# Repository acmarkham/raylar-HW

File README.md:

# raylar-HW
## Caracal Raylar Hardware Repo

This is the main repository for the bioacoustic platform Caracal Raylar. This is an updated version of the CARACAL EVO (2021) design, which itself is an evolution of SHUMBA (2019). The main features are:

- Six onboard microphones, low frequency rolloff 7Hz
- microSD card for storage
- Onboard GPS for precision timestamping and location
- Onboard dual band wireless (sub-GHz plus 2.4GHz) for mesh networking
- STM32U5 core, supports up to 3.5MB RAM depending on variant
- Multi-source power tree including
  - USB
  - Solar
  - Rechargeable single cell lipo
  - External battery 6V-12V
- Onboard accelerometer and magnetometer/compass for tilt and direction
- Extension connectors: 
  - QWIIC x 2 (easy to plug in peripherals like a OLED display) 
  - Mikrobus MBUS (supports a huge ecosystem of sensors)
  - EXT
  - DEBUG
- Beeper/LEDs for user feedback (errors, status etc)

## PCB

## Schematic

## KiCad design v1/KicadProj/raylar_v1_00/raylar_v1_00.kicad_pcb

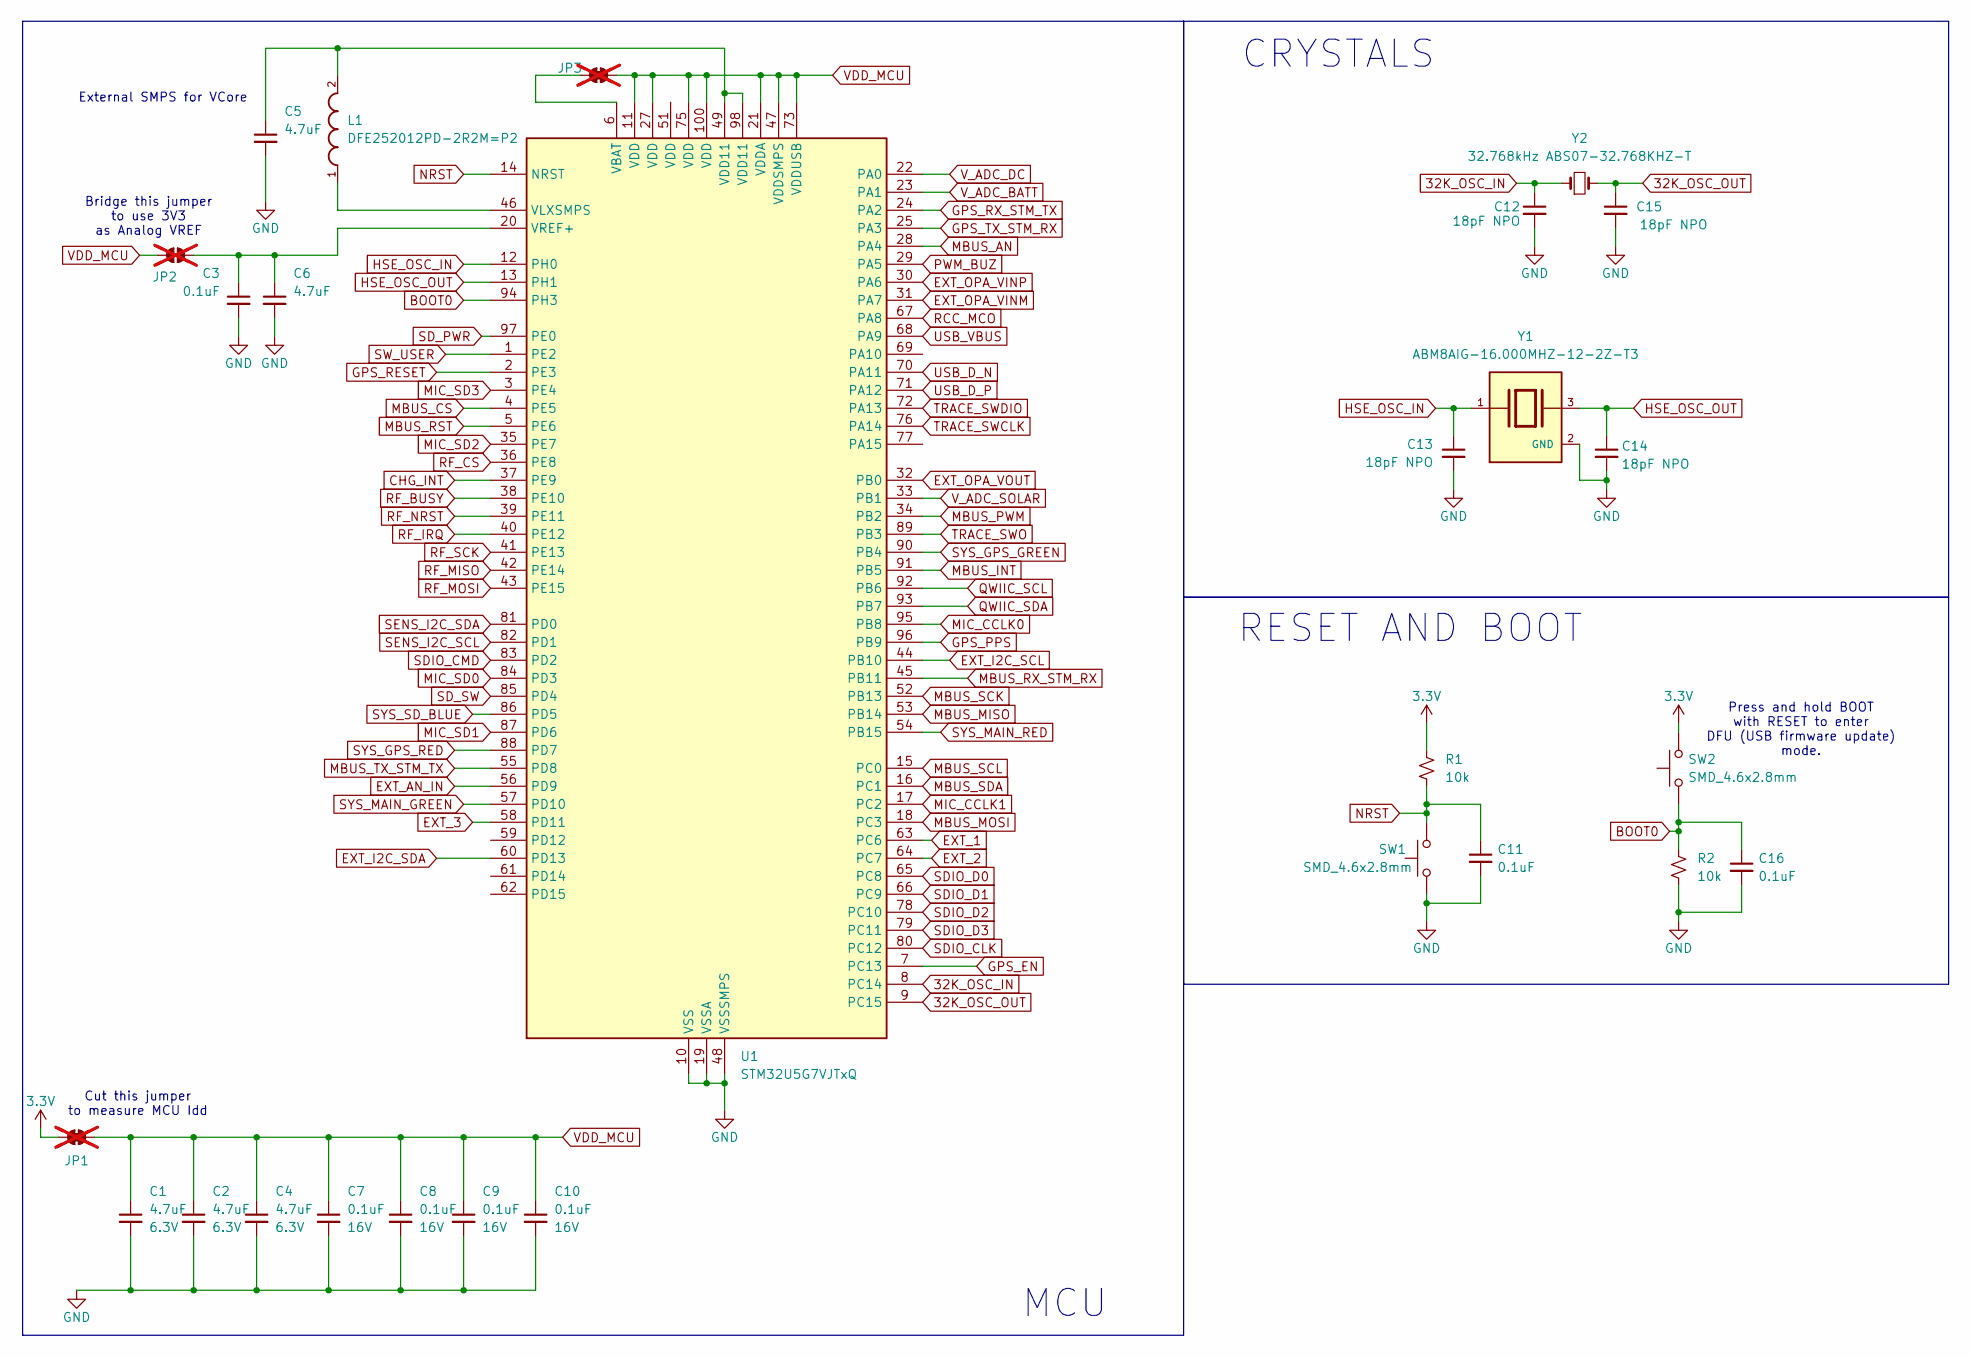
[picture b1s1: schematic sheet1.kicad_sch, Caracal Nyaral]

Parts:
C1, C2, C4, C5, C6: 4.7uF; C_0402_1005Metric; Voltage 6.3V; Tolerance 20%; LCSC C23733
C3, C7, C8, C9, C10, C11, C16: 0.1uF; C_0402_1005Metric; Voltage 16V; Tolerance 10%; LCSC C77020
C12, C13, C14, C15: 18pF NPO; C_0402_1005Metric; Voltage 50V; Tolerance 5%; LCSC C106202
JP1, JP3: Jumper_2_NC_Trace; not fitted
JP2: Jumper_2_NO; not fitted
L1: DFE252012PD-2R2M=P2; INDC2520X120N; Digikey 490-DFE252012PD-2R2M=P2DKR-ND
R1, R2: 10k; R_0402_1005Metric; LCSC C60489
SW1, SW2: SMD_4.6x2.8mm; Push_SMD_4.6x2.8mm_h1.9mm; Mfg Part# KMR231NGLFS; LCSC C221676
U1: STM32U5G7VJTxQ; LQFP-100_14x14mm_P0.5mm; LCSC C24591629
Y1: ABM8AIG-16.000MHZ-12-2Z-T3; XTAL_ABM8AIG-16.000MHZ-12-2Z-T3; PARTREV 43629; LCSC C596903
Y2: 32.768kHz ABS07-32.768KHZ-T; Crystal_SMD_3.2x1.5mm; LCSC C130253

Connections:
3.3V: JP1.1 (A), R1.2, SW2.2; also elsewhere on the board
32K_OSC_IN: C12.1, U1.8 (PC14), Y2.1
32K_OSC_OUT: C15.1, U1.9 (PC15), Y2.2
BOOT0: C16.1, R2.2, SW2.1, U1.94 (PH3)
CHG_INT: U1.37 (PE9); also elsewhere on the board
EXT_1: U1.63 (PC6); also elsewhere on the board
EXT_2: U1.64 (PC7); also elsewhere on the board
EXT_3: U1.58 (PD11); also elsewhere on the board
EXT_AN_IN: U1.56 (PD9); also elsewhere on the board
EXT_I2C_SCL: U1.44 (PB10); also elsewhere on the board
EXT_I2C_SDA: U1.60 (PD13); also elsewhere on the board
EXT_OPA_VINM: U1.31 (PA7); also elsewhere on the board
EXT_OPA_VINP: U1.30 (PA6); also elsewhere on the board
EXT_OPA_VOUT: U1.32 (PB0); also elsewhere on the board
GND: C1.2, C2.2, C3.2, C4.2, C5.2, C6.2, C7.2, C8.2, C9.2, C10.2, C11.2, C12.2, C13.2, C14.2, C15.2, C16.2, R2.1, SW1.1, U1.10 (VSS), U1.19 (VSSA), U1.26 (VSS), U1.48 (VSSSMPS), U1.50 (VSS), U1.74 (VSS), U1.99 (VSS), Y1.2 (GND), Y1.4 (GND); also elsewhere on the board
GPS_EN: U1.7 (PC13); also elsewhere on the board
GPS_PPS: U1.96 (PB9); also elsewhere on the board
GPS_RESET: U1.2 (PE3); also elsewhere on the board
GPS_RX_STM_TX: U1.24 (PA2); also elsewhere on the board
GPS_TX_STM_RX: U1.25 (PA3); also elsewhere on the board
HSE_OSC_IN: C13.1, U1.12 (PH0), Y1.1
HSE_OSC_OUT: C14.1, U1.13 (PH1), Y1.3
MBUS_AN: U1.28 (PA4); also elsewhere on the board
MBUS_CS: U1.4 (PE5); also elsewhere on the board
MBUS_INT: U1.91 (PB5); also elsewhere on the board
MBUS_MISO: U1.53 (PB14); also elsewhere on the board
MBUS_MOSI: U1.18 (PC3); also elsewhere on the board
MBUS_PWM: U1.34 (PB2); also elsewhere on the board
MBUS_RST: U1.5 (PE6); also elsewhere on the board
MBUS_RX_STM_RX: U1.45 (PB11); also elsewhere on the board
MBUS_SCK: U1.52 (PB13); also elsewhere on the board
MBUS_SCL: U1.15 (PC0); also elsewhere on the board
MBUS_SDA: U1.16 (PC1); also elsewhere on the board
MBUS_TX_STM_TX: U1.55 (PD8); also elsewhere on the board
MIC_CCLK0: U1.95 (PB8); also elsewhere on the board
MIC_CCLK1: U1.17 (PC2); also elsewhere on the board
MIC_SD0: U1.84 (PD3); also elsewhere on the board
MIC_SD1: U1.87 (PD6); also elsewhere on the board
MIC_SD2: U1.35 (PE7); also elsewhere on the board
MIC_SD3: U1.3 (PE4); also elsewhere on the board
NRST: C11.1, R1.1, SW1.2, U1.14 (NRST); also elsewhere on the board
unnamed: C5.1, L1.2, U1.49 (VDD11), U1.98 (VDD11)
unnamed: C3.1, C6.1, JP2.2 (B), U1.20 (VREF+)
unnamed: JP3.1 (A), U1.6 (VBAT)
unnamed: L1.1, U1.46 (VLXSMPS)
PWM_BUZ: U1.29 (PA5); also elsewhere on the board
QWIIC_SCL: U1.92 (PB6); also elsewhere on the board
QWIIC_SDA: U1.93 (PB7); also elsewhere on the board
RCC_MCO: U1.67 (PA8); also elsewhere on the board
RF_BUSY: U1.38 (PE10); also elsewhere on the board
RF_CS: U1.36 (PE8); also elsewhere on the board
RF_IRQ: U1.40 (PE12); also elsewhere on the board
RF_MISO: U1.42 (PE14); also elsewhere on the board
RF_MOSI: U1.43 (PE15); also elsewhere on the board
RF_NRST: U1.39 (PE11); also elsewhere on the board
RF_SCK: U1.41 (PE13); also elsewhere on the board
SDIO_CLK: U1.80 (PC12); also elsewhere on the board
SDIO_CMD: U1.83 (PD2); also elsewhere on the board
SDIO_D0: U1.65 (PC8); also elsewhere on the board
SDIO_D1: U1.66 (PC9); also elsewhere on the board
SDIO_D2: U1.78 (PC10); also elsewhere on the board
SDIO_D3: U1.79 (PC11); also elsewhere on the board
SD_PWR: U1.97 (PE0); also elsewhere on the board
SD_SW: U1.85 (PD4); also elsewhere on the board
SENS_I2C_SCL: U1.82 (PD1); also elsewhere on the board
SENS_I2C_SDA: U1.81 (PD0); also elsewhere on the board
SW_USER: U1.1 (PE2); also elsewhere on the board
SYS_GPS_GREEN: U1.90 (PB4); also elsewhere on the board
SYS_GPS_RED: U1.88 (PD7); also elsewhere on the board
SYS_MAIN_GREEN: U1.57 (PD10); also elsewhere on the board
SYS_MAIN_RED: U1.54 (PB15); also elsewhere on the board
SYS_SD_BLUE: U1.86 (PD5); also elsewhere on the board
TRACE_SWCLK: U1.76 (PA14); also elsewhere on the board
TRACE_SWDIO: U1.72 (PA13); also elsewhere on the board
TRACE_SWO: U1.89 (PB3); also elsewhere on the board
USB_D_N: U1.70 (PA11); also elsewhere on the board
USB_D_P: U1.71 (PA12); also elsewhere on the board
USB_VBUS: U1.68 (PA9); also elsewhere on the board
VDD_MCU: C1.1, C2.1, C4.1, C7.1, C8.1, C9.1, C10.1, JP1.2 (B), JP2.1 (A), JP3.2 (B), U1.11 (VDD), U1.21 (VDDA), U1.27 (VDD), U1.47 (VDDSMPS), U1.73 (VDDUSB), U1.75 (VDD), U1.100 (VDD)
V_ADC_BATT: U1.23 (PA1); also elsewhere on the board
V_ADC_DC: U1.22 (PA0); also elsewhere on the board
V_ADC_SOLAR: U1.33 (PB1); also elsewhere on the board

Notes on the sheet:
Press and hold BOOT with RESET to enter DFU (USB firmware update) mode.
CRYSTALS
MCU
Bridge this jumper to use 3V3 as Analog VREF
Cut this jumper to measure MCU Idd
RESET AND BOOT
External SMPS for VCore

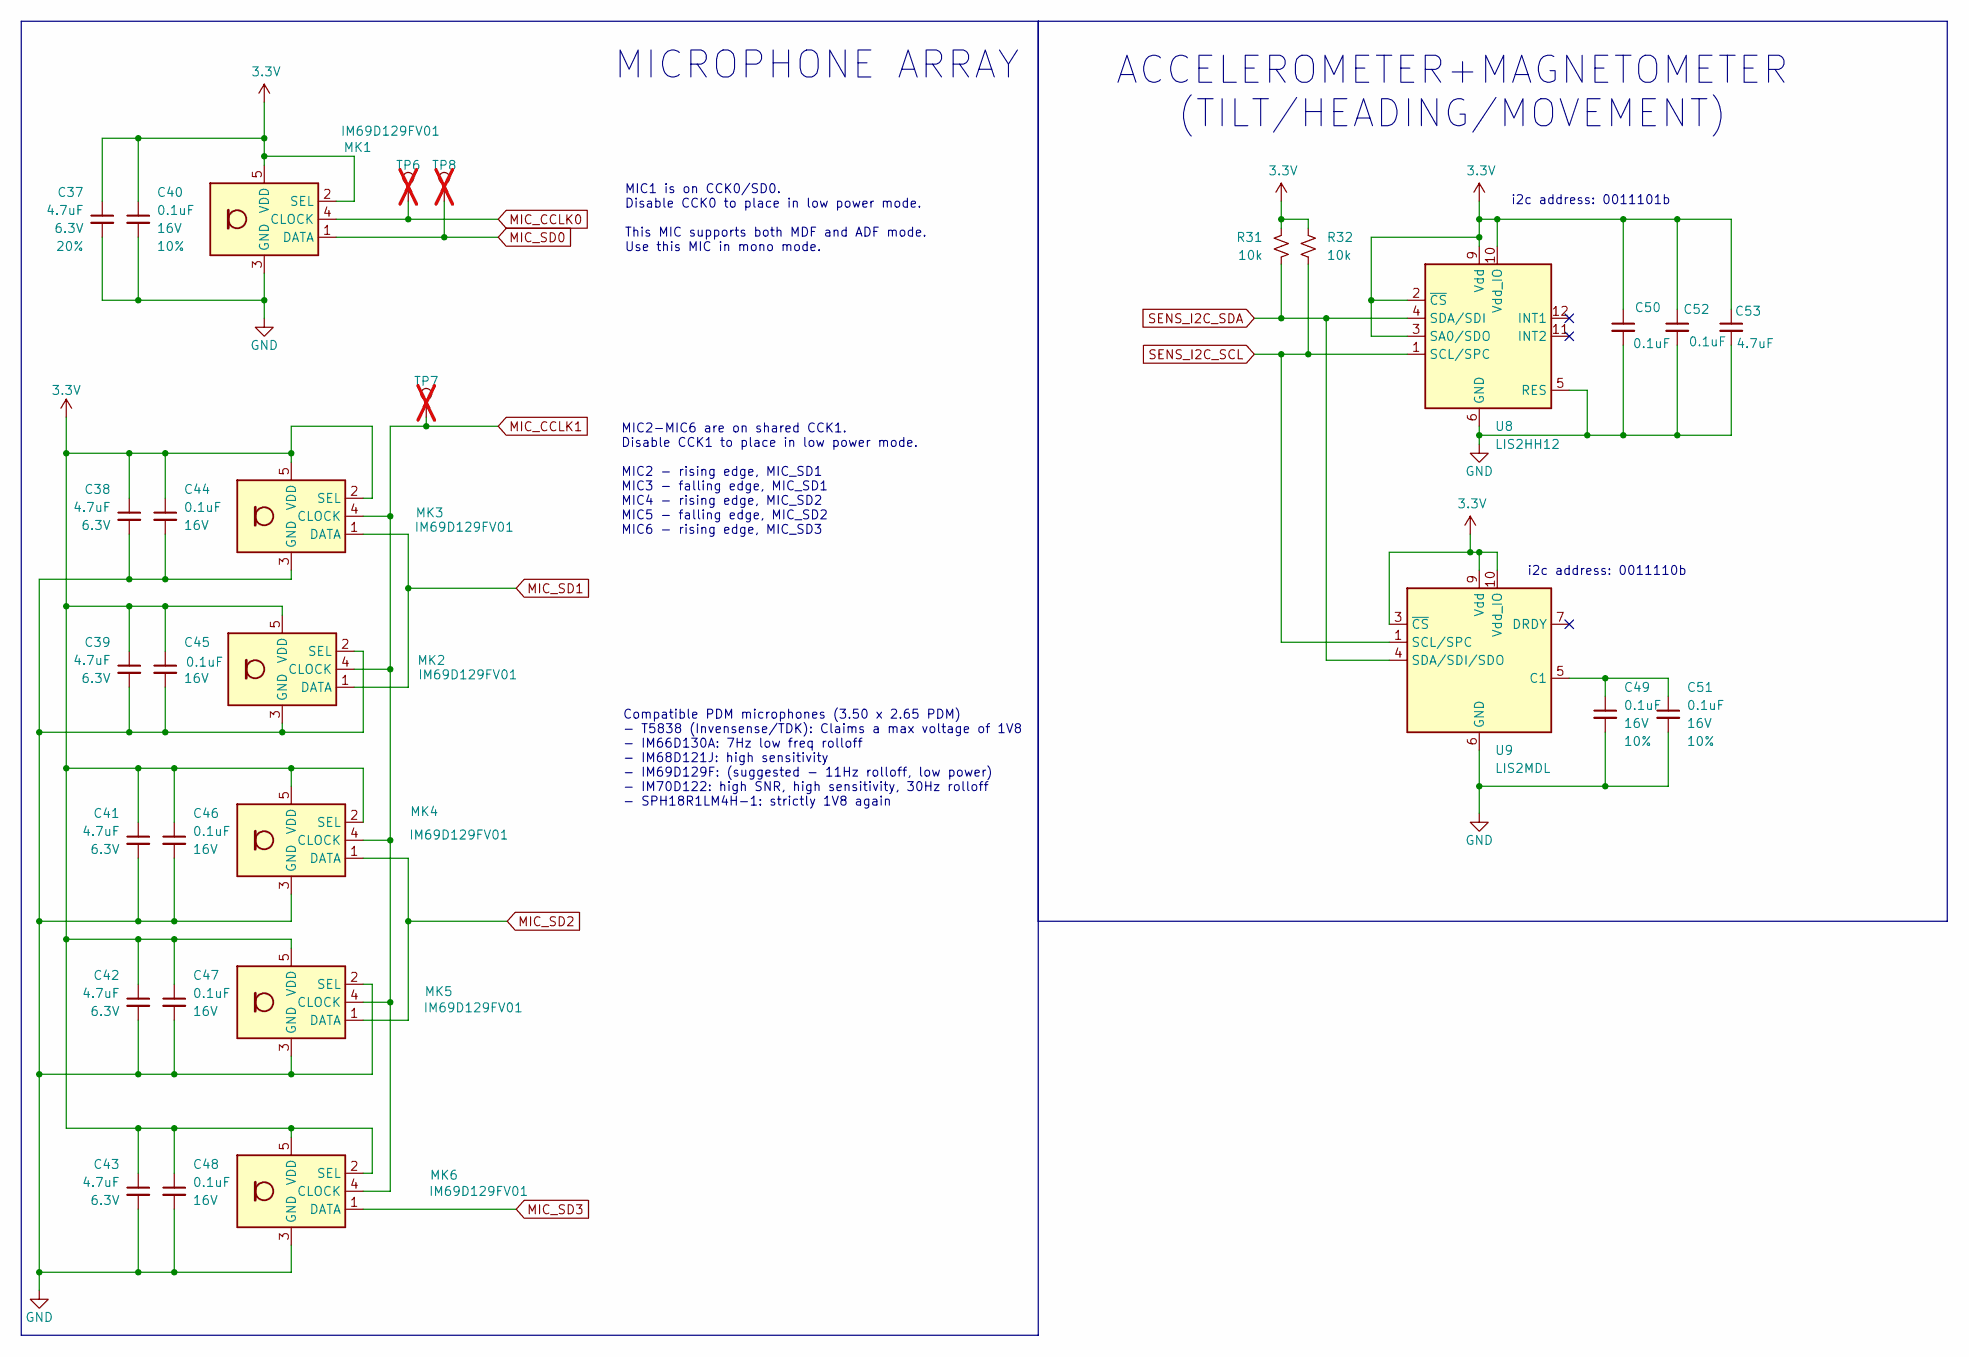
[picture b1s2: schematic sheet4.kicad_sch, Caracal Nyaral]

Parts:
C37, C38, C39, C41, C42, C43, C53: 4.7uF; C_0402_1005Metric; Voltage 6.3V; Tolerance 20%; LCSC C23733
C40, C44, C45, C46, C47, C48, C49, C50, C51, C52: 0.1uF; C_0402_1005Metric; Voltage 16V; Tolerance 10%; LCSC C77020
MK1, MK2, MK3, MK4, MK5, MK6: IM69D129FV01; Knowles_LGA-5_3.5x2.65mm; Digikey 448-IM69D129FV01XTMA1DKR-ND
R31, R32: 10k; R_0402_1005Metric; LCSC C60489
TP6, TP7, TP8: 0.5mm; TestPoint-0.5mm; not fitted
U8: LIS2HH12; LGA-12_2x2mm_P0.5mm; LCSC C221446
U9: LIS2MDL; LGA-12_2x2mm_P0.5mm; LCSC C919695

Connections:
3.3V: C37.1, C38.1, C39.1, C40.1, C41.1, C42.1, C43.1, C44.1, C45.1, C46.1, C47.1, C48.1, C50.1, C52.1, C53.1, MK1.2 (SEL), MK1.5 (VDD), MK2.5 (VDD), MK3.2 (SEL), MK3.5 (VDD), MK4.2 (SEL), MK4.5 (VDD), MK5.5 (VDD), MK6.2 (SEL), MK6.5 (VDD), R31.2, R32.2, U8.2 (~CS), U8.3 (SA0/SDO), U8.9 (Vdd), U8.10 (Vdd_IO), U9.3 (~CS), U9.9 (Vdd), U9.10 (Vdd_IO); also elsewhere on the board
GND: C37.2, C38.2, C39.2, C40.2, C41.2, C42.2, C43.2, C44.2, C45.2, C46.2, C47.2, C48.2, C49.2, C50.2, C51.2, C52.2, C53.2, MK1.3 (GND), MK2.2 (SEL), MK2.3 (GND), MK3.3 (GND), MK4.3 (GND), MK5.2 (SEL), MK5.3 (GND), MK6.3 (GND), U8.5 (RES), U8.6 (GND), U8.7 (GND), U8.8 (GND), U9.6 (GND), U9.8 (GND); also elsewhere on the board
MIC_CCLK0: MK1.4 (CLOCK), TP6.1; also elsewhere on the board
MIC_CCLK1: MK2.4 (CLOCK), MK3.4 (CLOCK), MK4.4 (CLOCK), MK5.4 (CLOCK), MK6.4 (CLOCK), TP7.1; also elsewhere on the board
MIC_SD0: MK1.1 (DATA), TP8.1; also elsewhere on the board
MIC_SD1: MK2.1 (DATA), MK3.1 (DATA); also elsewhere on the board
MIC_SD2: MK4.1 (DATA), MK5.1 (DATA); also elsewhere on the board
MIC_SD3: MK6.1 (DATA); also elsewhere on the board
unnamed: C49.1, C51.1, U9.5 (C1)
SENS_I2C_SCL: R32.1, U8.1 (SCL/SPC), U9.1 (SCL/SPC); also elsewhere on the board
SENS_I2C_SDA: R31.1, U8.4 (SDA/SDI), U9.4 (SDA/SDI/SDO); also elsewhere on the board

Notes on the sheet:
MICROPHONE ARRAY
Compatible PDM microphones (3.50 x 2.65 PDM) - T5838 (Invensense/TDK): Claims a max voltage of 1V8 - IM66D130A: 7Hz low freq rolloff - IM68D121J: high sensitivity - IM69D129F: (suggested - 11Hz rolloff, low power) - IM70D122: high SNR, high sensitivity, 30Hz rolloff - SPH18R1LM4H-1: strictly 1V8 ag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
i2c address: 0011101b
MIC2-MIC6 are on shared CCK1. Disable CCK1 to place in low power mode. MIC2 - rising edge, MIC_SD1 MIC3 - falling edge, MIC_SD1 MIC4 - rising edge, MIC_SD2 MIC5 - falling edge, MIC_SD2 MIC6 - rising edge, MIC_SD3
i2c address: 0011110b
MIC1 is on CCK0/SD0. Disable CCK0 to place in low power mode. This MIC supports both MDF and ADF mode. Use this MIC in mono mode.
ACCELEROMETER+MAGNETOMETER (TILT/HEADING/MOVEMENT)

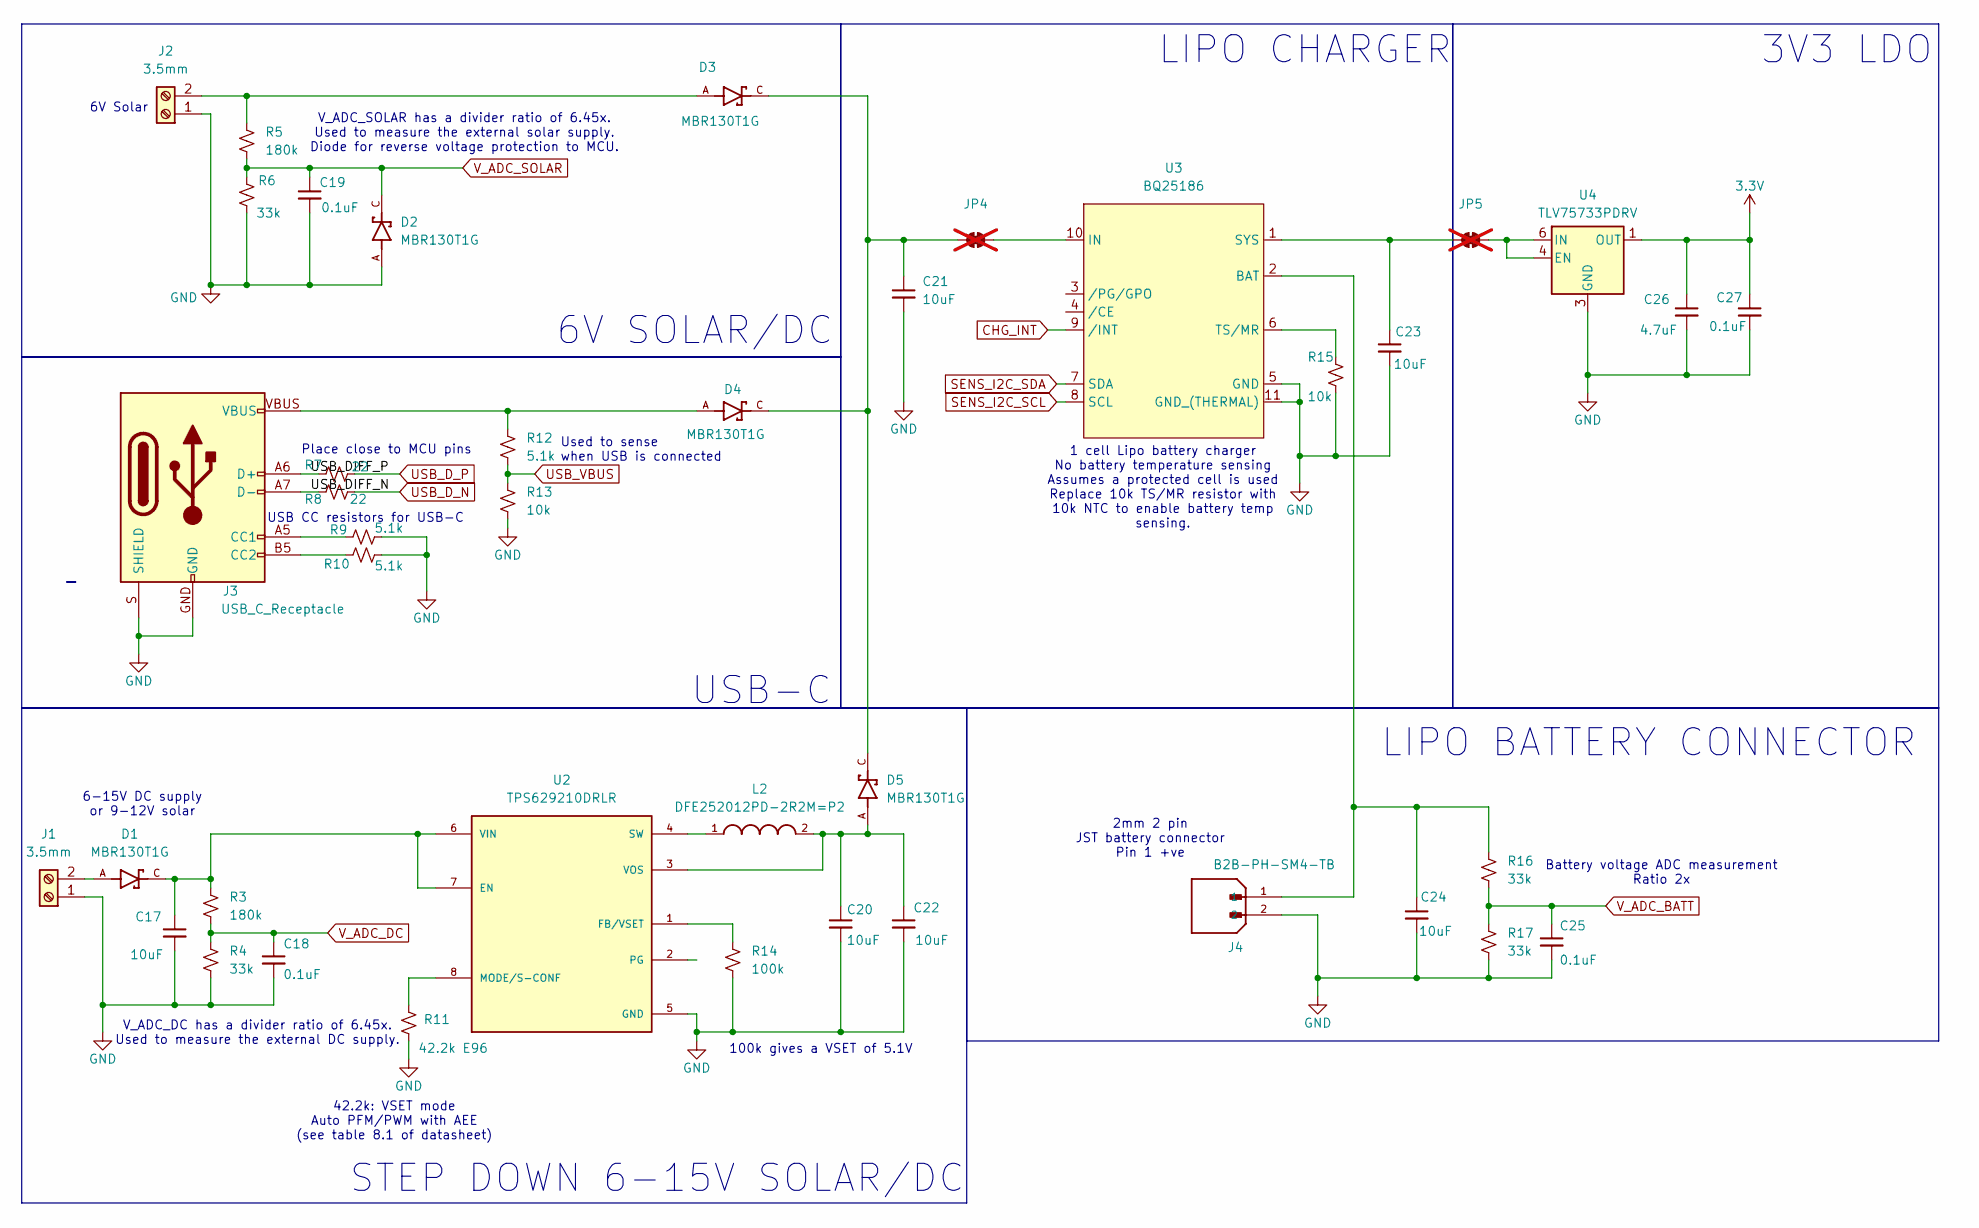
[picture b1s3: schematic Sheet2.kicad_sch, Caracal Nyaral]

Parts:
C17, C20, C21, C22, C23, C24: 10uF; C_0805_2012Metric; Voltage 25V; Tolerance 10%; LCSC C2932476
C18, C19, C25, C27: 0.1uF; C_0402_1005Metric; Voltage 16V; Tolerance 10%; LCSC C77020
C26: 4.7uF; C_0402_1005Metric; Voltage 6.3V; Tolerance 20%; LCSC C23733
D1, D2, D3, D4, D5: MBR130T1G; DIO_MBR0530T1G; PARTREV 9; LCSC C82461
J1, J2: 3.5mm; ScrewTerminal_1x02_P3.5mm_Horizontal_Black; LCSC C695629
J3: USB_C_Receptacle; USB-C_16; LCSC C2988369
J4: B2B-PH-SM4-TB; JST_B2B-PH-SM4-TB; PARTREV N/A; LCSC C160352
JP4, JP5: Jumper_2_NC_Trace; not fitted
L2: DFE252012PD-2R2M=P2; INDC2520X120N; Digikey 490-DFE252012PD-2R2M=P2DKR-ND
R3, R5: 180k; R_0402_1005Metric; LCSC C138046
R4, R6, R16, R17: 33k; R_0402_1005Metric; LCSC C25779
R7, R8: 22; R_0402_1005Metric; LCSC C25092
R9, R10, R12: 5.1k; R_0402_1005Metric; LCSC C25905
R11: 42.2k E96; R_0402_1005Metric; LCSC C276270
R13, R15: 10k; R_0402_1005Metric; LCSC C60489
R14: 100k; R_0402_1005Metric; LCSC C25741
U2: TPS629210DRLR; SOT50P160X60-8N; PARTREV B; LCSC C5219301
U3: BQ25186; IC_BQ25185DLHR; LCSC C44639442
U4: TLV75733PDRV; WDFN-6_2x2mm; LCSC C2868428

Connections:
3.3V: C26.1, C27.1, U4.1 (OUT); also elsewhere on the board
/Sheet2/USB_DIFF_N: J3.A7 (D-), J3.B7 (D-), R8.1
/Sheet2/USB_DIFF_P: J3.A6 (D+), J3.B6 (D+), R7.1
CHG_INT: U3.9 (/INT); also elsewhere on the board
GND: C17.2, C18.2, C19.2, C20.2, C21.2, C22.2, C23.2, C24.2, C25.2, C26.2, C27.2, D2.A, J1.1, J2.1, J3.GND, J3.S (SHIELD), J4.2, R4.1, R6.1, R9.2, R10.2, R11.1, R13.1, R14.1, R15.1, R17.1, U2.5 (GND), U3.5 (GND), U3.11 (GND_(THERMAL)), U4.3 (GND), U4.7 (GND); also elsewhere on the board
unnamed: D4.A, J3.VBUS, R12.2
unnamed: D1.A, J1.2
unnamed: D3.A, J2.2, R5.2
unnamed: J3.A5 (CC1), R9.1
unnamed: J3.B5 (CC2), R10.1
unnamed: C21.1, D3.C, D4.C, D5.C, JP4.1 (A)
unnamed: JP4.2 (B), U3.10 (IN)
unnamed: C23.1, JP5.1 (A), U3.1 (SYS)
unnamed: JP5.2 (B), U4.4 (EN), U4.6 (IN)
unnamed: C17.1, D1.C, R3.2, U2.6 (VIN), U2.7 (EN)
unnamed: R14.2, U2.1 (FB/VSET)
unnamed: R11.2, U2.8 (MODE/S-CONF)
unnamed: L2.1, U2.4 (SW)
unnamed: C20.1, C22.1, D5.A, L2.2, U2.3 (VOS)
unnamed: C24.1, J4.1, R16.2, U3.2 (BAT)
unnamed: R15.2, U3.6 (TS/MR)
SENS_I2C_SCL: U3.8 (SCL); also elsewhere on the board
SENS_I2C_SDA: U3.7 (SDA); also elsewhere on the board
USB_D_N: R8.2; also elsewhere on the board
USB_D_P: R7.2; also elsewhere on the board
USB_VBUS: R12.1, R13.2; also elsewhere on the board
V_ADC_BATT: C25.1, R16.1, R17.2; also elsewhere on the board
V_ADC_DC: C18.1, R3.1, R4.2; also elsewhere on the board
V_ADC_SOLAR: C19.1, D2.C, R5.1, R6.2; also elsewhere on the board

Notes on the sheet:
100k gives a VSET of 5.1V
Used to sense when USB is connected
6V Solar
Battery voltage ADC measurement Ratio 2x
6-15V DC supply or 9-12V solar
3V3 LDO
STEP DOWN 6-15V SOLAR/DC
LIPO BATTERY CONNECTOR
1 cell Lipo battery charger No battery temperature sensing Assumes a protected cell is used Replace 10k TS/MR resistor with 10k NTC to enable battery temp sensing.
42.2k: VSET mode Auto PFM/PWM with AEE (see table 8.1 of datasheet)
V_ADC_DC has a divider ratio of 6.45x. Used to measure the external DC supply.
6V SOLAR/DC
USB-C
LIPO CHARGER
Place close to MCU pins
2mm 2 pin JST battery connector Pin 1 +ve
V_ADC_SOLAR has a divider ratio of 6.45x. Used to measure the external solar supply. Diode for reverse voltage protection to MCU.
USB CC resistors for USB-C

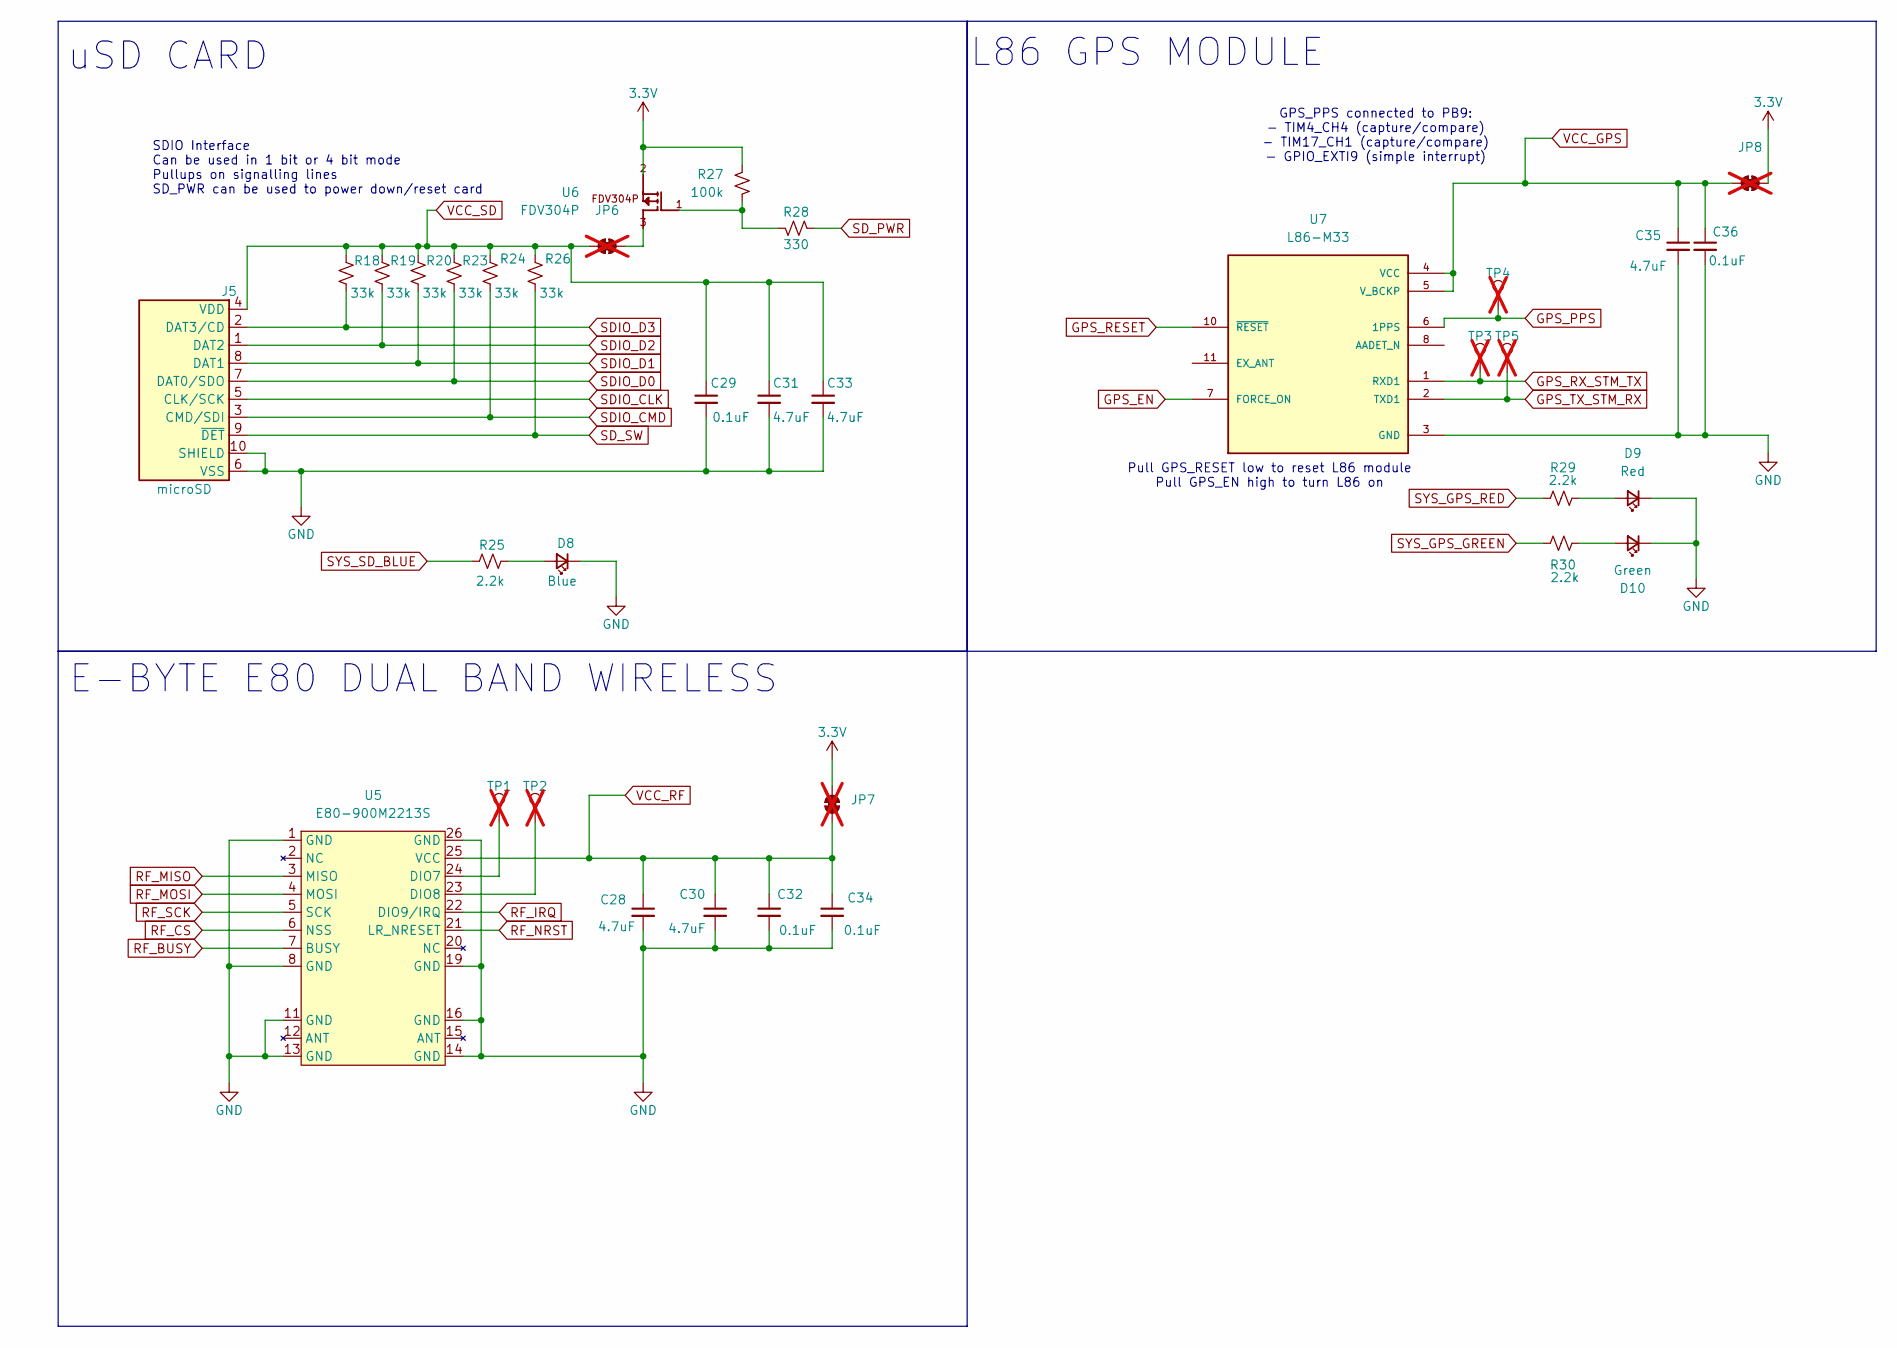
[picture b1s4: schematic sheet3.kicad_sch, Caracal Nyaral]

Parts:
C28, C30, C31, C33, C35: 4.7uF; C_0402_1005Metric; Voltage 6.3V; Tolerance 20%; LCSC C23733
C29, C32, C34, C36: 0.1uF; C_0402_1005Metric; Voltage 16V; Tolerance 10%; LCSC C77020
D8: Blue; LED_0603_1608Metric_Blue; LCSC C19171394
D9: Red; LED_0603_1608Metric_Red; LCSC C19171390
D10: Green; LED_0603_1608Metric_Green; LCSC C19273151
J5: microSD; microSD_External_Pin; LCSC C20619272
JP6, JP7, JP8: Jumper_2_NC_Trace; not fitted
R18, R19, R20, R23, R24, R26: 33k; R_0402_1005Metric; LCSC C25779
R25, R29, R30: 2.2k; R_0402_1005Metric; LCSC C25879
R27: 100k; R_0402_1005Metric; LCSC C25741
R28: 330; R_0402_1005Metric; LCSC C25104
TP1, TP2, TP3, TP4, TP5: 0.5mm; TestPoint-0.5mm; not fitted
U5: E80-900M2213S; E80-x00M2213S; LCSC C42464134
U6: FDV304P; SOT23-3; LCSC C10884
U7: L86-M33; XCVR_L86-M33; LCSC C909689

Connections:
3.3V: JP7.2 (B), JP8.2 (B), R27.2, U6.2; also elsewhere on the board
GND: C28.2, C29.2, C30.2, C31.2, C32.2, C33.2, C34.2, C35.2, C36.2, D8.1 (K), D9.1 (K), D10.1 (K), J5.6 (VSS), J5.10 (SHIELD), U5.1 (GND), U5.8 (GND), U5.11 (GND), U5.13 (GND), U5.14 (GND), U5.16 (GND), U5.19 (GND), U5.26 (GND), U7.3 (GND), U7.12 (GND); also elsewhere on the board
GPS_EN: U7.7 (FORCE_ON); also elsewhere on the board
GPS_PPS: TP4.1, U7.6 (1PPS); also elsewhere on the board
GPS_RESET: U7.10 (~RESET); also elsewhere on the board
GPS_RX_STM_TX: TP3.1, U7.1 (RXD1); also elsewhere on the board
GPS_TX_STM_RX: TP5.1, U7.2 (TXD1); also elsewhere on the board
unnamed: D8.2 (A), R25.2
unnamed: D9.2 (A), R29.2
unnamed: D10.2 (A), R30.2
unnamed: JP6.2 (B), U6.3
unnamed: R27.1, R28.2, U6.1
unnamed: TP1.1, U5.24 (DIO7)
unnamed: TP2.1, U5.23 (DIO8)
RF_BUSY: U5.7 (BUSY); also elsewhere on the board
RF_CS: U5.6 (NSS); also elsewhere on the board
RF_IRQ: U5.22 (DIO9/IRQ); also elsewhere on the board
RF_MISO: U5.3 (MISO); also elsewhere on the board
RF_MOSI: U5.4 (MOSI); also elsewhere on the board
RF_NRST: U5.21 (LR_NRESET); also elsewhere on the board
RF_SCK: U5.5 (SCK); also elsewhere on the board
SDIO_CLK: J5.5 (CLK/SCK); also elsewhere on the board
SDIO_CMD: J5.3 (CMD/SDI), R24.1; also elsewhere on the board
SDIO_D0: J5.7 (DAT0/SDO), R23.1; also elsewhere on the board
SDIO_D1: J5.8 (DAT1), R20.1; also elsewhere on the board
SDIO_D2: J5.1 (DAT2), R19.1; also elsewhere on the board
SDIO_D3: J5.2 (DAT3/CD), R18.1; also elsewhere on the board
SD_PWR: R28.1; also elsewhere on the board
SD_SW: J5.9 (~DET), R26.1; also elsewhere on the board
SYS_GPS_GREEN: R30.1; also elsewhere on the board
SYS_GPS_RED: R29.1; also elsewhere on the board
SYS_SD_BLUE: R25.1; also elsewhere on the board
VCC_GPS: C35.1, C36.1, JP8.1 (A), U7.4 (VCC), U7.5 (V_BCKP)
VCC_RF: C28.1, C30.1, C32.1, C34.1, JP7.1 (A), U5.25 (VCC)
VCC_SD: C29.1, C31.1, C33.1, J5.4 (VDD), JP6.1 (A), R18.2, R19.2, R20.2, R23.2, R24.2, R26.2

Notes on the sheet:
E-BYTE E80 DUAL BAND WIRELESS
Pull GPS_RESET low to reset L86 module Pull GPS_EN high to turn L86 on
L86 GPS MODULE
GPS_PPS connected to PB9: - TIM4_CH4 (capture/compare) - TIM17_CH1 (capture/compare) - GPIO_EXTI9 (simple interrupt)
SDIO Interface Can be used in 1 bit or 4 bit mode Pullups on signalling lines SD_PWR can be used to power down/reset card
uSD CARD
